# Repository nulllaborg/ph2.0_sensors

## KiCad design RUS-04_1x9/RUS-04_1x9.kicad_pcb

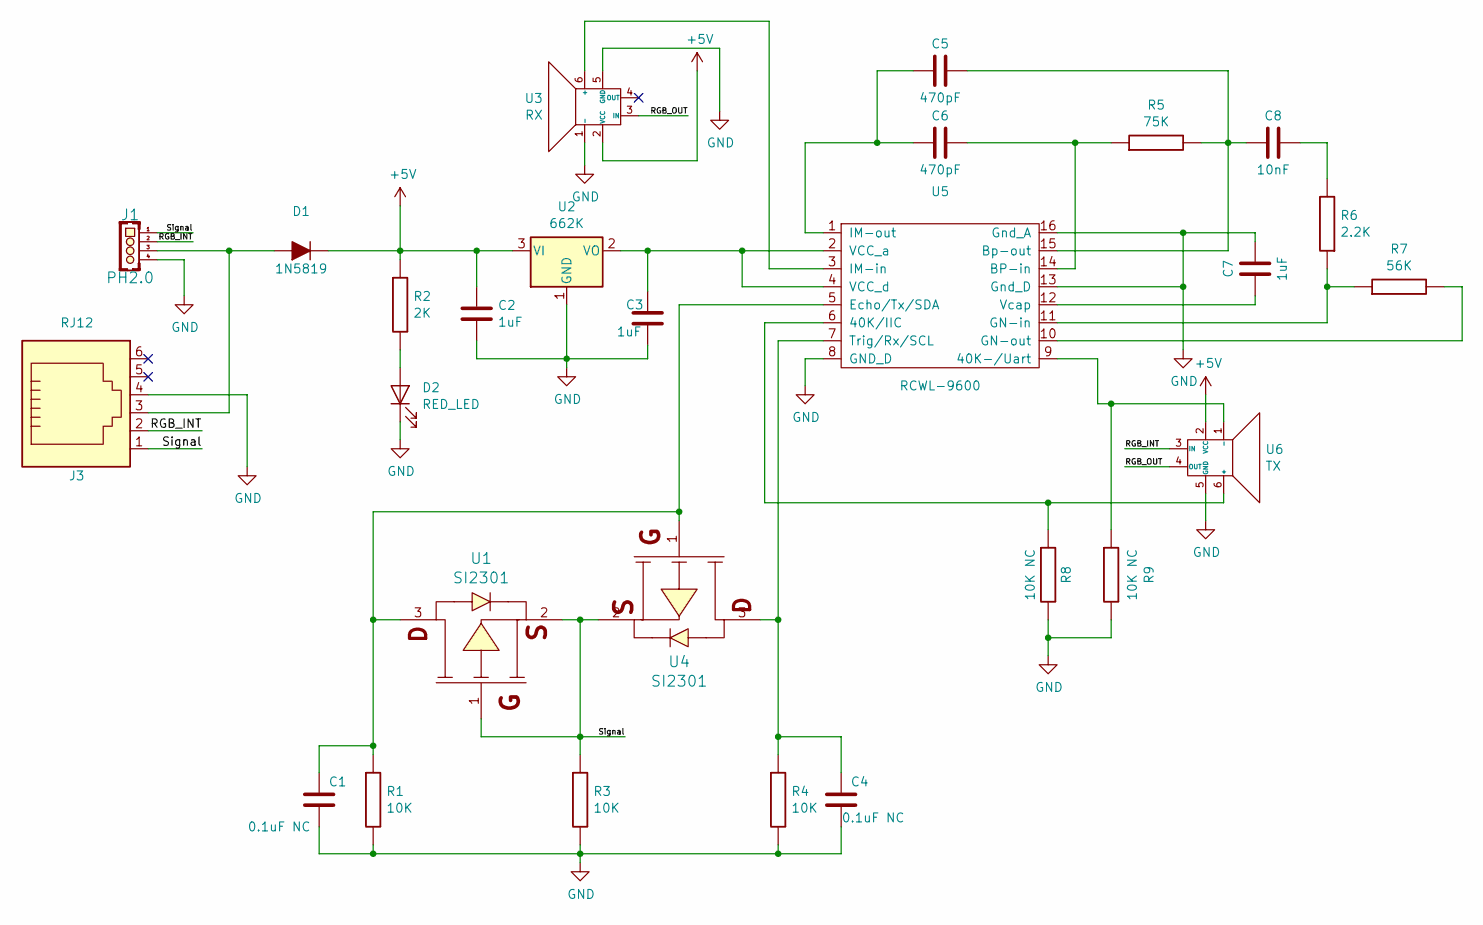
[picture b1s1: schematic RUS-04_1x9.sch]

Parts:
C1, C4: 0.1uF NC; C_0603
C2, C3, C7: 1uF; C_0603
C5, C6: 470pF; C_0603
C8: 10nF; C_0603
D1: 1N5819; D_SOD-123
D2: RED_LED; LED_0603
J1: PH2.0; DIP-PH2.00mm-4A
J3: RJ12; SMD-RJ25
R1, R3, R4: 10K; R_0603
R2: 2K; R_0603
R5: 75K; R_0603
R6: 2.2K; R_0603
R7: 56K; R_0603
R8, R9: 10K NC; R_0603
U1, U4: SI2301; SOT-23
U2: 662K; SOT-23
U3: RX; RGB-Ultrasonic-6PIN-1.2mm
U5: RCWL-9600; SOIC-16W_7.5x10.3mm_Pitch1.27mm
U6: TX; RGB-Ultrasonic-6PIN-1.2mm

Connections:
+5V: C2.1, D1.1 (-), R2.1, U2.3 (VI), U3.2 (VCC), U6.2 (VCC)
/RGB_INT: J1.2, J3.2, U6.3 (IN)
/RGB_OUT: U3.3 (IN), U6.4 (OUT)
/Signal: J1.1, J3.1, R3.1, U1.1, U1.2, U4.2
GND: C1.2, C2.2, C3.2, C4.2, C7.2, D2.1 (K), J1.4, J3.4, R1.2, R3.2, R4.2, R8.2, R9.2, U2.1 (GND), U3.1 (-), U3.5 (GND), U5.8 (GND_D), U5.13 (Gnd_D), U5.16 (Gnd_A), U6.5 (GND)
unnamed: C1.1, R1.1, U1.3, U4.1, U5.5 (Echo/Tx/SDA)
unnamed: C3.1, U2.2 (VO), U5.2 (VCC_a), U5.4 (VCC_d)
unnamed: C4.1, R4.1, U4.3, U5.7 (Trig/Rx/SCL)
unnamed: C5.1, C6.1, U5.1 (IM-out)
unnamed: C5.2, C8.1, R5.2, U5.15 (Bp-out)
unnamed: C6.2, R5.1, U5.14 (BP-in)
unnamed: C7.1, U5.12 (Vcap)
unnamed: C8.2, R6.2
unnamed: D1.2 (+), J1.3, J3.3
unnamed: D2.2 (A), R2.2
unnamed: R6.1, R7.1, U5.11 (GN-in)
unnamed: R7.2, U5.10 (GN-out)
unnamed: R8.1, U5.6 (40K/IIC), U6.6 (+)
unnamed: R9.1, U5.9 (40K-/Uart), U6.1 (-)
unnamed: U3.6 (+), U5.3 (IM-in)

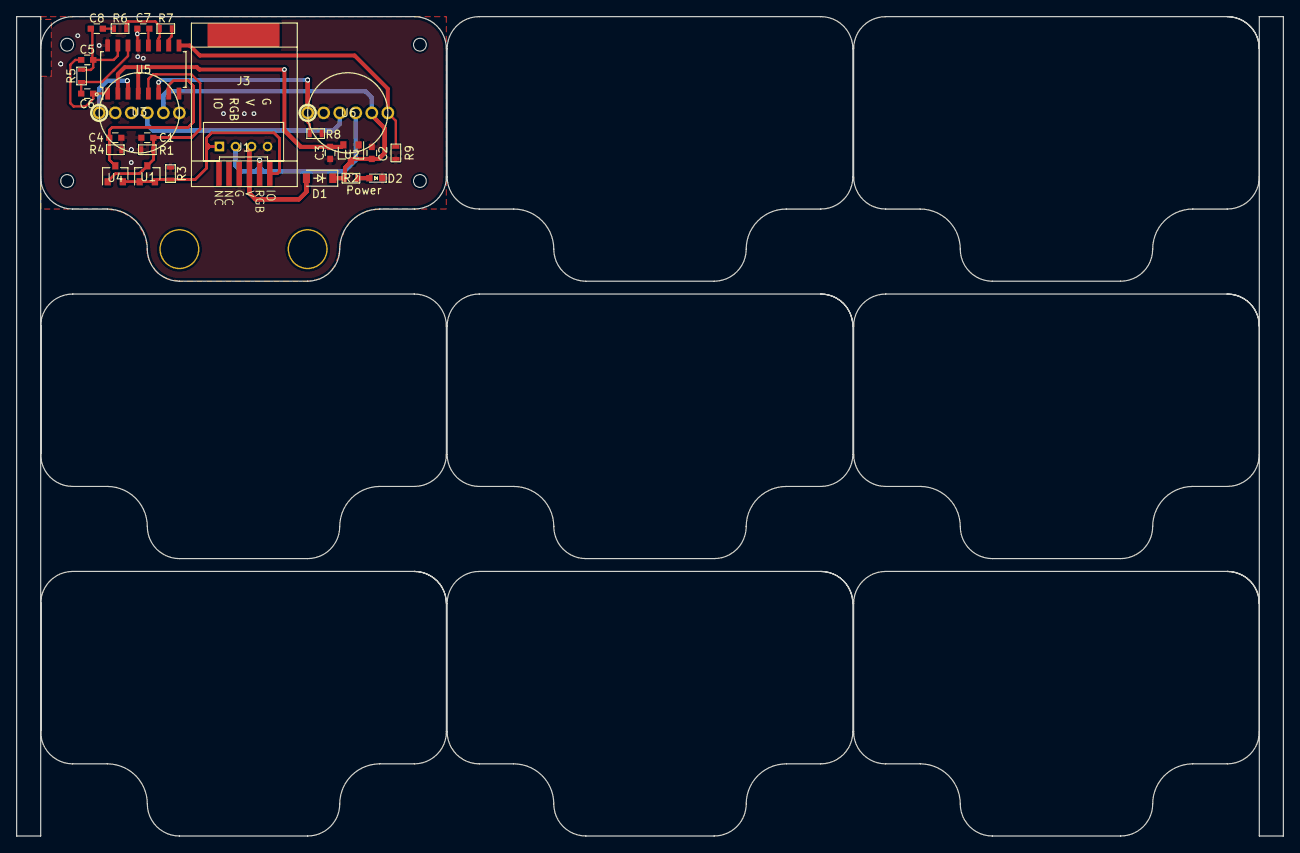
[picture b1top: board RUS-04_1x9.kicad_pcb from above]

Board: 2 copper layers, 158.0 x 102.2 mm, 27 parts (0 on the bottom side), 20 nets.

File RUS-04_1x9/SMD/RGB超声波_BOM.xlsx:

Comment | Description | Designator | Footprint | LibRef | Pins | Quantity | 备注 | url
1uF | desc | C2,C3,C7, | C_0603 | libref | 2 | 3
470pF | desc | C5,C6, | C_0603 | libref | 2 | 2
10nF | desc | C8, | C_0603 | libref | 2 | 1
1N5819 | desc | D1, | D_SOD-123 | libref | 2 | 1
BLUE_LED | desc | D2, | LED_0603 | libref | 2 | 1
10K | desc | R1,R3,R4, | R_0603 | libref | 2 | 3
2K | desc | R2, | R_0603 | libref | 2 | 1
75K |  | R5, | R_0603 | libref | 2 | 1
56K |  | R7, | R_0603 |  | 2 | 1
2.2K | desc | R6, | R_0603 | libref | 2 | 1
SI2301 | desc | U1,U4, | SOT-23 | libref | 3 | 2
662K | desc | U2, | SOT-23 | libref | 3 | 1
RCWL-9600 | desc | U5, | SOIC-16W_7.5x10.3mm_Pitch1.27mm | libref | 16 | 1
PH2.0 | desc | J1, | DIP-PH2.00mm-4A | libref | 4 | 1 | PH2.0 4Pin直插
RX | desc | U3, | RGB-Ultrasonic-6PIN-1.2mm | libref | 6 | 1 | 自供
TX | desc | U6, | RGB-Ultrasonic-6PIN-1.2mm | libref | 6 | 1 | 自供

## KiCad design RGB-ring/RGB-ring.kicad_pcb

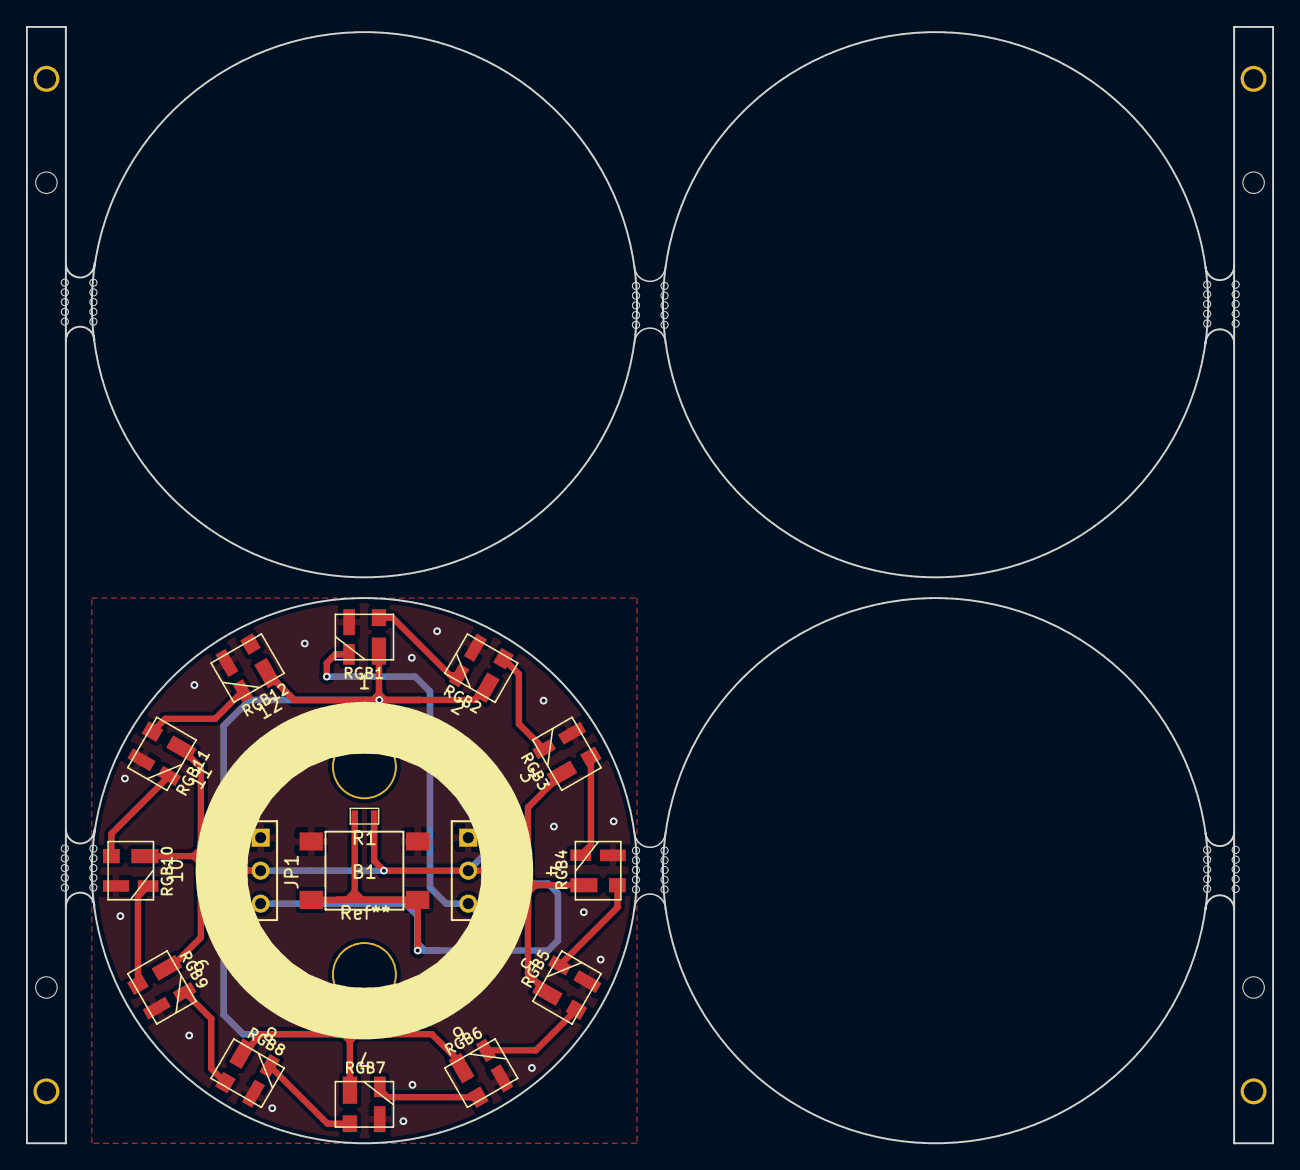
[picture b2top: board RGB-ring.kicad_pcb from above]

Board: 2 copper layers, 96.0 x 86.0 mm, 18 parts (1 on the bottom side), 15 nets.

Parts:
B1: Button_2; Button_6 x 6
J1: PH2.0; SMD-Horizontal-PH2.00mm-4P
JP1, JP2: JACK3; DIP-1.5Hole-2.54mm-Pitch-3P
R1: 4.7K; R_0603
RGB1, RGB2, RGB3, RGB4, RGB5, RGB7, RGB8, RGB9, RGB10, RGB11, RGB12: WS2812; LED_FGGWS3535-2812
RGB6: WS2812; New_LED_FGGWS3535-2812
Ref**: Hole-3x5mm-2

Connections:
+5V: J1.3, JP1.2, JP2.2, R1.1, RGB1.1, RGB2.1, RGB3.1, RGB4.1, RGB5.1, RGB6.1, RGB7.1, RGB8.1, RGB9.1, RGB10.1, RGB11.1, RGB12.1
/Button: B1.3, B1.4, J1.2, JP1.3, R1.2
/OUT1: RGB4.2, RGB5.4
/OUT2: RGB8.2, RGB9.4
/RGB_IN: J1.1, JP2.3, RGB1.4
GND: B1.1, B1.2, J1.4, JP1.1, JP2.1, RGB1.3, RGB2.3, RGB3.3, RGB4.3, RGB5.3, RGB6.3, RGB7.3, RGB8.3, RGB9.3, RGB10.3, RGB11.3, RGB12.3
unnamed: RGB1.2, RGB2.4
unnamed: RGB2.2, RGB3.4
unnamed: RGB3.2, RGB4.4
unnamed: RGB5.2, RGB6.4
unnamed: RGB6.2, RGB7.4
unnamed: RGB7.2, RGB8.4
unnamed: RGB10.2, RGB11.4
unnamed: RGB9.2, RGB10.4
unnamed: RGB11.2, RGB12.4

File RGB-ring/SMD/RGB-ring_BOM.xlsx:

RGB灯环
Comment | Description | Designator | Footprint | LibRef | Pins | Quantity | 备注
Button_2 | 高按键，高度6mm | B1, | Button_6 x 6 | LibRef | 4 | 1
4.7K | Desc | R1, | R_0603 | LibRef | 2 | 1 | 总数量按盘装
WS2812 | Desc | RGB12,RGB11,RGB10,RGB9,RGB8,RGB7,RGB6,,RGB5,RGB4,RGB3,RGB2,RGB1, | LED_FGGWS3535-2812 | LibRef | 4 | 12 | 易创提供
PH2.0 | Desc | J1, | SMD-Horizontal-PH2.00mm-4P | LibRef | 6 | 1 | 4Pin PH2.0卧贴

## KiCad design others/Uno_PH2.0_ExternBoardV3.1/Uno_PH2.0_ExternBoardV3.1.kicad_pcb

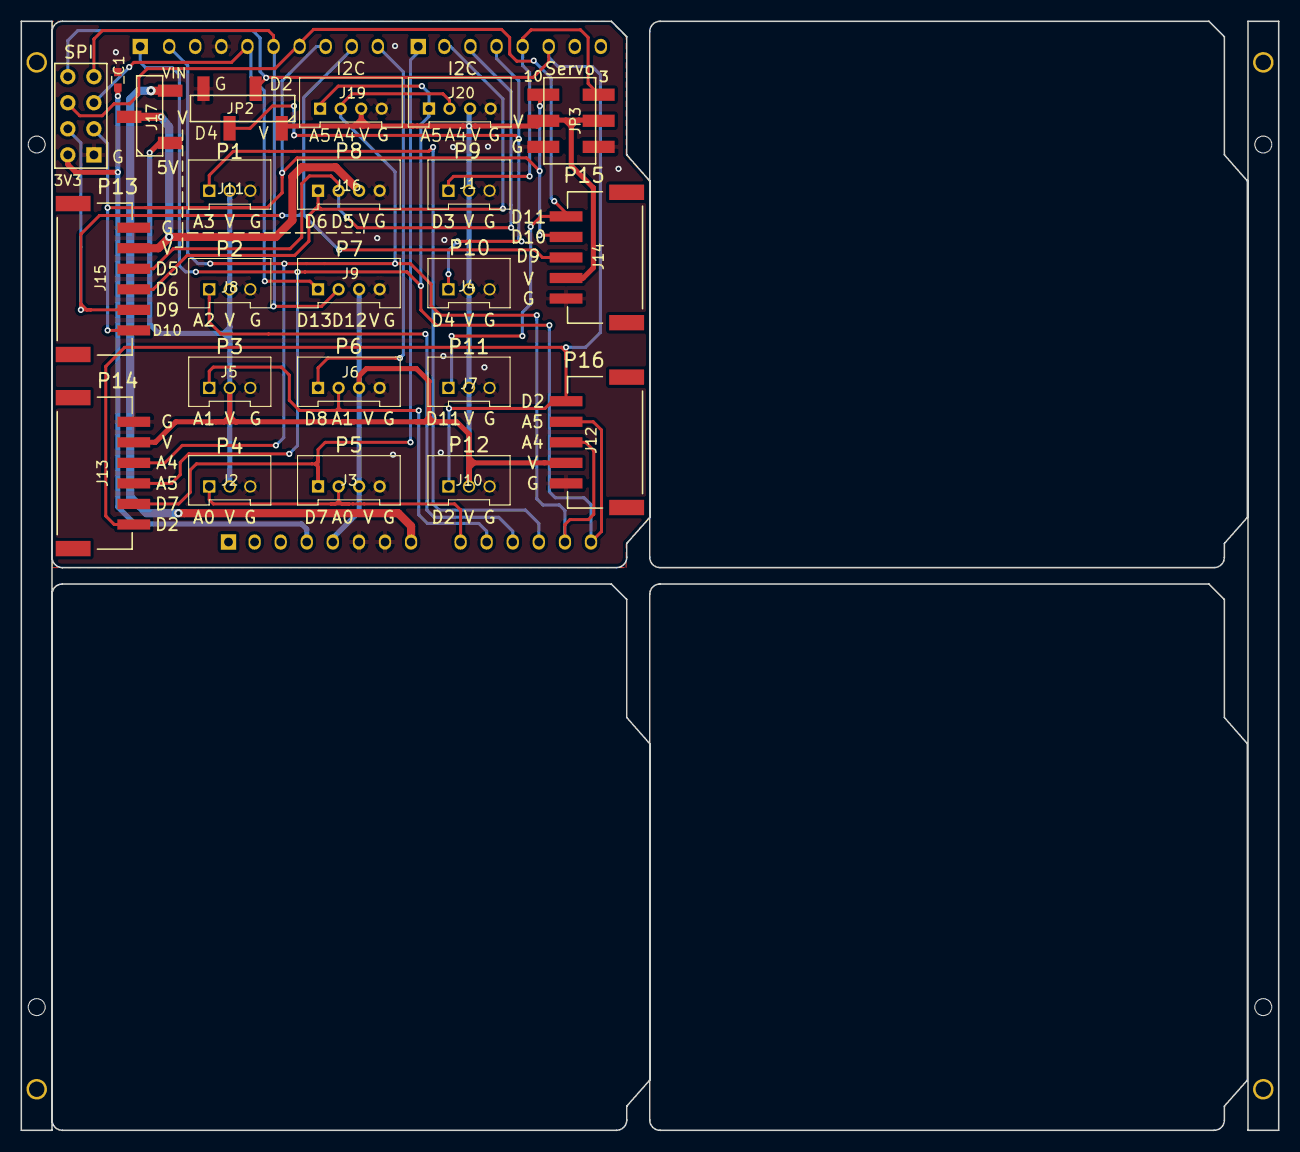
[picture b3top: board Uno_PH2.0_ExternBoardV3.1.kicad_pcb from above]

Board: 2 copper layers, 122.4 x 108.0 mm, 24 parts (0 on the bottom side), 23 nets.

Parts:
C1: 10uF; C_0603
J1, J2, J4, J5, J7, J8, J10, J11: Edge_Con3; DIP-PH2.00mm-3A
J3, J16: Edge_Con4; DIP-PH2.00mm-4A
J6, J9: 4pin; DIP-PH2.00mm-4A
J12, J14: Edge_Con5; SMD-Horizontal-PH2.00mm-5P
J13, J15: Edge_Con6; SMD-Horizontal-PH2.00mm-6P
J17: JACK_CAP; SMD-2.54mm-Pitch-3P
J19, J20: I2C; DIP-PH2.00mm-4A
JP1: nRF24L01+; DIP-1.5Hole-2.54mm-Pitch-4Px2
JP2: Ultrasoud; SMD-2.54mm-Pitch-4P
JP3: Servo*2; SMD_3x2P_2.54mm
U1: ArduinoUnoR3

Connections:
+3V3: C1.1, JP1.8, U1.4
+5V: J1.2, J2.2, J3.3, J4.2, J5.2, J6.3, J7.2, J8.2, J9.3, J10.2, J11.2, J12.4, J13.5, J14.4, J17.1, J19.3, J20.3, JP2.1, JP3.2, JP3.5, U1.5
/A0: J2.1, J3.2, U1.9
/A1: J5.1, J6.2, U1.10
/A2: J8.1, U1.11
/A3: J11.1, U1.12
/D2: J10.1, J12.1, J13.1, JP1.5, JP2.2, U1.17
/D3: J1.1, JP3.6, U1.18
/D4: J4.1, JP2.3, U1.19
/D5: J15.4, J16.2, U1.20
/D6: J15.3, J16.1, U1.21
/D7: J3.1, J13.2, U1.22
/D8: J6.1, U1.23
/D9: J14.3, J15.2, JP1.7, U1.24
/D10: J14.2, J15.1, JP1.2, JP3.1, U1.25
/D11: J7.1, J14.1, JP1.6, U1.26
/D12: J9.2, JP1.4, U1.27
/D13: J9.1, JP1.3, U1.28
/SCL: J12.2, J13.3, J19.1, J20.1, U1.14, U1.32
/SDA: J12.3, J13.4, J19.2, J20.2, U1.13, U1.31
GND: C1.2, J1.3, J2.3, J3.4, J4.3, J5.3, J6.4, J7.3, J8.3, J9.4, J10.3, J11.3, J12.5, J13.6, J14.5, J15.6, J16.4, J19.4, J20.4, JP1.1, JP2.4, JP3.3, JP3.4, U1.6, U1.7, U1.29
VIN: J17.3, U1.8
VSS: J15.5, J16.3, J17.2

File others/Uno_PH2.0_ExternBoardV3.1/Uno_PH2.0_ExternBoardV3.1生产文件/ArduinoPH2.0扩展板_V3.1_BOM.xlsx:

ArduinoUnoPH2.0扩展板V3.1
Comment | Description | Designator | Footprint | LibRef | Pins | Quantity | 链接
10uF | desc | C1, | C_0603 | libref | 2 | 1
Edge_Con5（卧贴） | desc | J12,J14, | SMD-Horizontal-PH2.00mm-5P | libref | 7 | 2
Edge_Con6（卧贴） | desc | J13,J15, | SMD-Horizontal-PH2.00mm-6P | libref | 8 | 2
贴片3Pin错位排针_黑色（右上） | desc | J17, | SMD-2.54mm-Pitch-3P | libref | 3 | 1 | https://item.taobao.com/item.htm?id=641124259762&ali_trackid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
贴片4Pin错位排母_黑色（右上） | desc | JP2, | SMD-2.54mm-Pitch-4P | libref | 4 | 1 | https://item.taobao.com/item.htm?id=622435185276&ali_trackid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
Edge_Con3 PH2.0 3A | desc | J1,J2,J4,J5,J7,J8,J10,J11, | DIP-PH2.00mm-3A | libref | 3 | 8 | 要普通长针
Edge_Con4 PH2.0 4A | desc | J3,J16,J6,J9,J19,J20, | DIP-PH2.00mm-4A | libref | 4 | 6 | 要普通长针
ArduinoUnoR3 | U1 |  | DIP-PH2.54mm | 32 | 1 | 蓝色排针6pin*1 红色排针8pin*1 蓝色排针8pin*1 黑色排针10Pin*1 | 定制短脚
贴片双排排针(黑色) | desc | JP3, | SMD_3x2P_2.54mm | libref | 6 | 1
跳线帽（红色） | desc |  |  |  | 1 |  | https://detail.tmall.com/item.htm?id=563996848564&ali_tracki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

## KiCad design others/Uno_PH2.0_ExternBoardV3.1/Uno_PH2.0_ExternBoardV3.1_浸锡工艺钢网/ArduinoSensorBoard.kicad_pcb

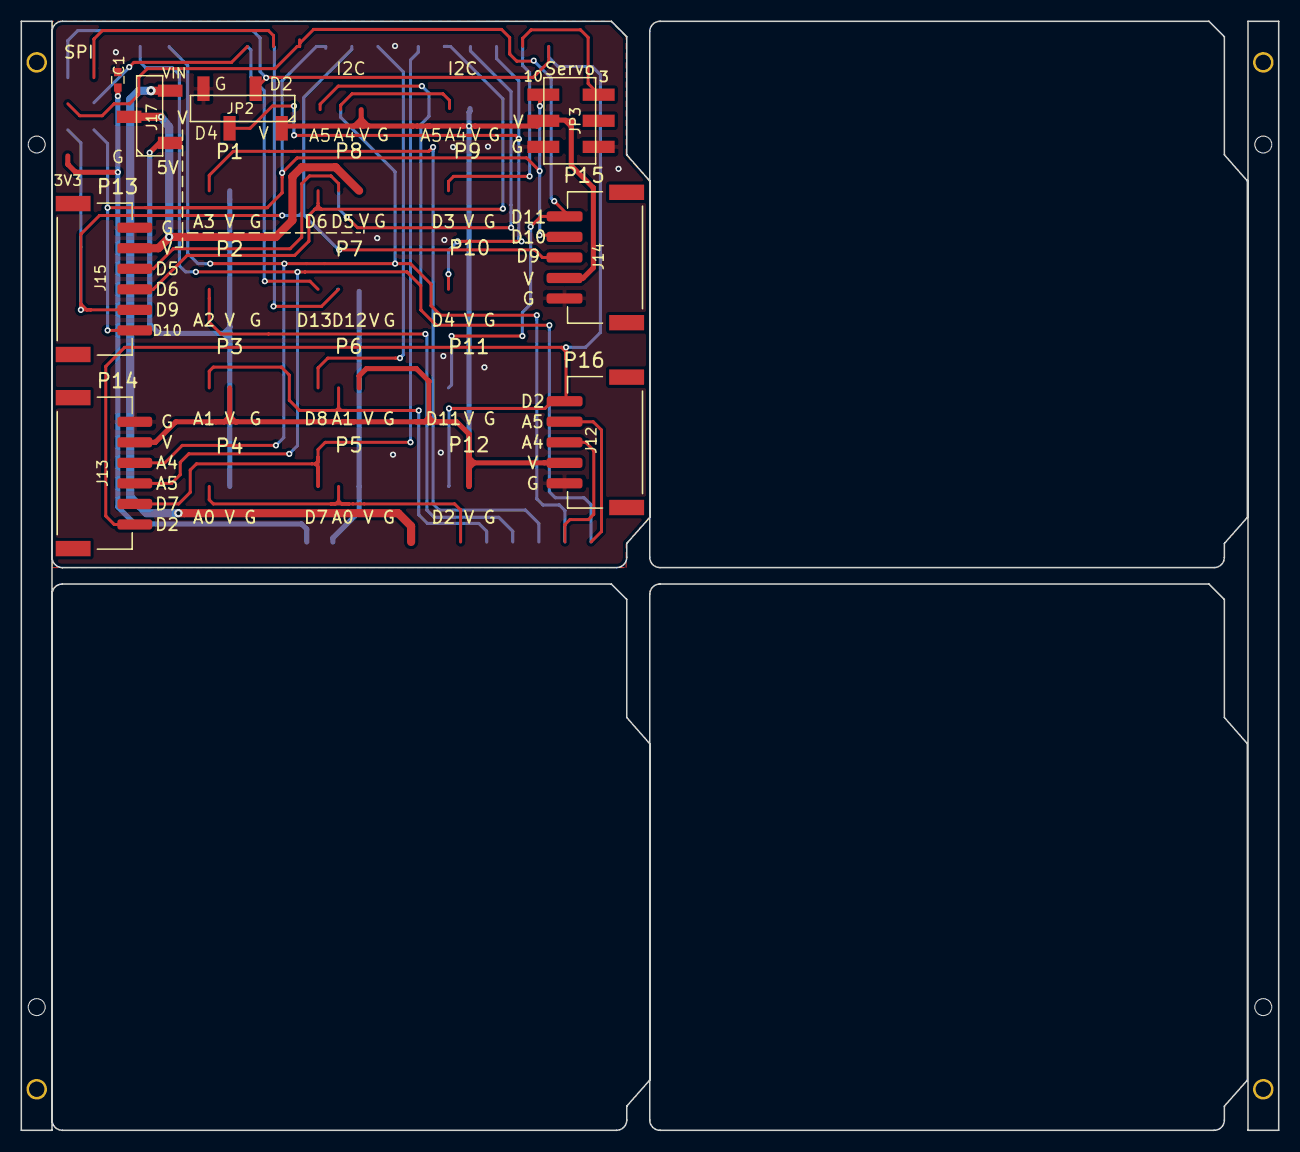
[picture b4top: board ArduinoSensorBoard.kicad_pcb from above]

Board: 2 copper layers, 122.4 x 108.0 mm, 8 parts (0 on the bottom side), 8 nets.

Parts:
C1: 10uF; C_0603
J12, J14: Edge_Con5; SMD-5P钢网
J13: Edge_Con6; SMD-6P钢网
J15: Edge_Con6; SMD-Horizontal-PH2.00mm-6P
J17: JACK_CAP; SMD-2.54mm-Pitch-3P
JP2: Ultrasoud; SMD-2.54mm-Pitch-4P
JP3: Servo*2; SMD_3x2P_2.54mm

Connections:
+5V: J12.4, J13.5, J14.4, J17.1, JP2.1, JP3.2, JP3.5
/D2: J12.1, J13.1, JP2.2
/D9: J14.3, J15.2
/D10: J14.2, J15.1, JP3.1
/SCL: J12.2, J13.3
/SDA: J12.3, J13.4
GND: C1.2, J12.5, J13.6, J14.5, J15.6, JP2.4, JP3.3, JP3.4
VSS: J15.5, J17.2

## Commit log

2022-05-11 增加优化后的传感器生产资料
